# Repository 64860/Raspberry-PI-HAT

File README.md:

# ⚙️ Raspberry Pi HAT KiCad Design

<div align="center">

 <!-- Image 1 -->

**A foundational KiCad design project for a custom Raspberry Pi HAT.**

</div>

## 📖 Overview

This repository contains the complete KiCad project files for a Raspberry Pi HAT (Hardware Attached on Top) expansion board. It provides the schematic and PCB layout files, enabling hardware enthusiasts, makers, and engineers to explore, modify, and manufacture their own custom HATs. Whether you're looking to integrate specific sensors, add custom I/O, or create a power management solution, this design serves as an excellent starting point for developing custom hardware for the Raspberry Pi.

## ✨ Features

-   **Complete KiCad Project**: All necessary files (`.kicad_pro`, `.kicad_sch`, `.kicad_pcb`) for a Raspberry Pi HAT.
-   **Standard HAT Form Factor**: Designed to meet Raspberry Pi HAT specifications for proper mounting and connection.
-   **Clear Schematic**: Detailed electrical diagram for easy understanding and modification of component connections.
-   **Optimized PCB Layout**: Ready for manufacturing, with consideration for signal integrity and component placement.
-   **Visual Renders**: Includes PNG images showing the 3D representation of the HAT design.
-   **Manufacturing Ready**: Easily generate Gerber files, Bill of Materials (BOM), and pick-and-place files from the project.

## 🖥️ Design Renders

<div align="center">

_Top view of the Raspberry Pi HAT design._

_Bottom view of the Raspberry Pi HAT design._

</div>

## 🛠️ Tools & Technologies

-   **EDA Software**: KiCad EDA Suite
-   **Hardware Platform**: Raspberry Pi

## 🚀 Getting Started

To explore or modify this HAT design, you'll need to have KiCad installed on your system.

### Prerequisites

-   **KiCad EDA Suite**: Version 7.0 or newer is recommended. Download from [kicad.org](https://www.kicad.org/download/).

### Installation & Setup

1.  **Clone the repository**
    ```bash
    git clone https://github.com/64860/Raspberry-PI-HAT.git
    cd Raspberry-PI-HAT
    ```

2.  **Open the project in KiCad**
    -   Launch KiCad.
    -   Go to `File` > `Open Project...`
    -   Navigate to the cloned repository directory and select `Raspberry PI HAT.kicad_pro`.

    You can now view the schematic, PCB layout, and 3D viewer.

## 📁 Project Structure

This project follows a standard KiCad project structure:

```
Raspberry-PI-HAT/
├── Raspberry PI HAT-backups/  # Automated KiCad backup files
├── Raspberry PI HAT.kicad_pcb  # Main PCB layout file
├── Raspberry PI HAT.kicad_prl  # KiCad project-local settings
├── Raspberry PI HAT.kicad_pro  # KiCad project file (entry point)
├── Raspberry PI HAT.kicad_sch  # Main schematic file
├── Raspberry PI HAT.png        # Rendered image of the HAT (e.g., 3D view)
├── Raspberry PI HAT2.png       # Another rendered image (e.g., bottom view)
└── fp-info-cache               # KiCad footprint information cache
```

-   `Raspberry PI HAT.kicad_pro`: The central project file that links the schematic and PCB.
-   `Raspberry PI HAT.kicad_sch`: Contains the circuit diagram, defining component connections and netlists.
-   `Raspberry PI HAT.kicad_pcb`: Holds the physical layout of the circuit board, including component footprints, trace routing, and layers.
-   `.png` files: Visual representations of the HAT design, useful for quick previews.

## 🔧 Manufacturing

Once you've finalized your design, you can generate manufacturing files directly from KiCad:

1.  **Generate Gerbers**: In the PCB editor (`.kicad_pcb`), go to `File` > `Plot...` to generate Gerber files (`.gbr`) for PCB fabrication.
2.  **Generate BOM (Bill of Materials)**: In the schematic editor (`.kicad_sch`), go to `Tools` > `Generate Bill of Materials...` to create a list of all components.
3.  **Generate Pick-and-Place File**: In the PCB editor, go to `File` > `Fabrication Outputs` > `Footprint Position File (.pos)` for automated assembly.

## 🤝 Contributing

We welcome contributions to improve this Raspberry Pi HAT design. If you have suggestions for enhancements, bug fixes, or new features, please feel free to:

1.  Fork the repository.
2.  Create a new branch (`git checkout -b feature/YourFeature`).
3.  Make your changes and commit them (`git commit -m 'Add some feature'`).
4.  Push to the branch (`git push origin feature/YourFeature`).
5.  Open a Pull Request.

Please ensure your KiCad version is compatible with the project.

## 📄 License

This project is licensed under the [LICENSE_NAME](LICENSE) - see the LICENSE file for details.
<!-- TODO: Add actual license file and name, e.g., MIT License -->

## 🙏 Acknowledgments

-   Built with [KiCad EDA Suite](https://www.kicad.org/)
-   Inspired by the versatile [Raspberry Pi](https://www.raspberrypi.com/) platform

## 📞 Support & Contact

-   🐛 Issues: [GitHub Issues](https://github.com/64860/Raspberry-PI-HAT/issues)

---

<div align="center">

**⭐ Star this repo if you find this design helpful!**

Made with ❤️ by [64860](https://github.com/64860)

</div>

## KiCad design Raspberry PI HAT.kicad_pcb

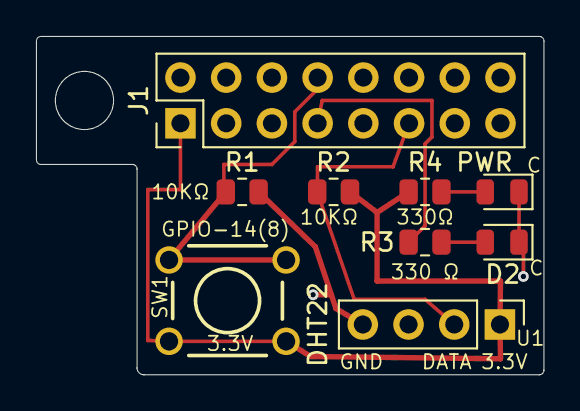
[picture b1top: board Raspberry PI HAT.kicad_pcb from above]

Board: 2 copper layers, 28.2 x 18.8 mm, 9 parts (0 on the bottom side), 7 nets.

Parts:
D2: LED; LED_0805_2012Metric
J1: Raspberry_Pi_2_3; PinHeader_2x08_P2.54mm_Vertical
PWR: LED; LED_0805_2012Metric
R1, R2: 10KΩ; R_0805_2012Metric
R3: 330 Ω; R_0805_2012Metric
R4: 330Ω; R_0805_2012Metric
SW1: SW_DPST; SW_PUSHBUTTON_PTH
U1: DHT22; PinHeader_1x04_P2.54mm_Vertical

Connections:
/3V3: J1.1 (3V3), R2.1, R4.1, SW1.1, U1.1 (VDD)
/Button_input: J1.8 (GPIO14/TXD), R1.1, SW1.2
GND: D2.1 (K), J1.6 (GND), J1.9 (GND), J1.14 (GND), PWR.1 (K), R1.2, U1.4 (GND)
unnamed: PWR.2 (A), R3.2
unnamed: D2.2 (A), R4.2
unnamed: J1.7 (GCLK0/GPIO4), R3.1
unnamed: J1.11 (GPIO17), R2.2, U1.2 (DATA)

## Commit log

2026-02-17 First and final commit
2026-02-17 Initialize README for Raspberry Pi HAT project
    Add README.md with project overview and instructions
